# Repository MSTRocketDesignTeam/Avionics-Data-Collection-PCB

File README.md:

# Overview

This repository contains the PCB design files and accompanying firmware for the Data Collection Board of the S&T Rocket Design Team's SRAD Avionics system.

## Purpose and Motivation
The goal of this project is to create flight-rate PCBs that can collect information about the teams rockets as they are launched.

## Inspirations

Initial developments of this board are to be more or less a direct replacement for a Telemetrum V3, with features and design optimizations to be implemented in future revisions.

A [Telemetrum V3](https://altusmetrum.org/TeleMetrum/) is an amateur rocketry telemetry solution from [Altus Metrum](https://altusmetrum.org/index.html).

[Signal](https://bps.space/signal/) from [BPS.Space](https://bps.space/) is a flight computer first and a data collection solution second. It is designed to stream data to the ground station, although it is likely insufficient for the large 10-30k ft class rockets that our team constructs.

There is also a really cool KiCad tutorial around making a small thumb drive sized pcb with an STM32, RF, and USB components. The link is [here on youtube by Phil's Lab](https://www.youtube.com/watch?v=14_jh3nLSsU) and is a great tutorial on using circuit design software and the process/approach you go through making something like this. Highly recommended to watch and maybe take some notes on, and a pretty solid start for our telemetry board.

# Features

#### Physical

#### Primary Components

#### Sensors

#### Data

#### Power

# Companion Documentation

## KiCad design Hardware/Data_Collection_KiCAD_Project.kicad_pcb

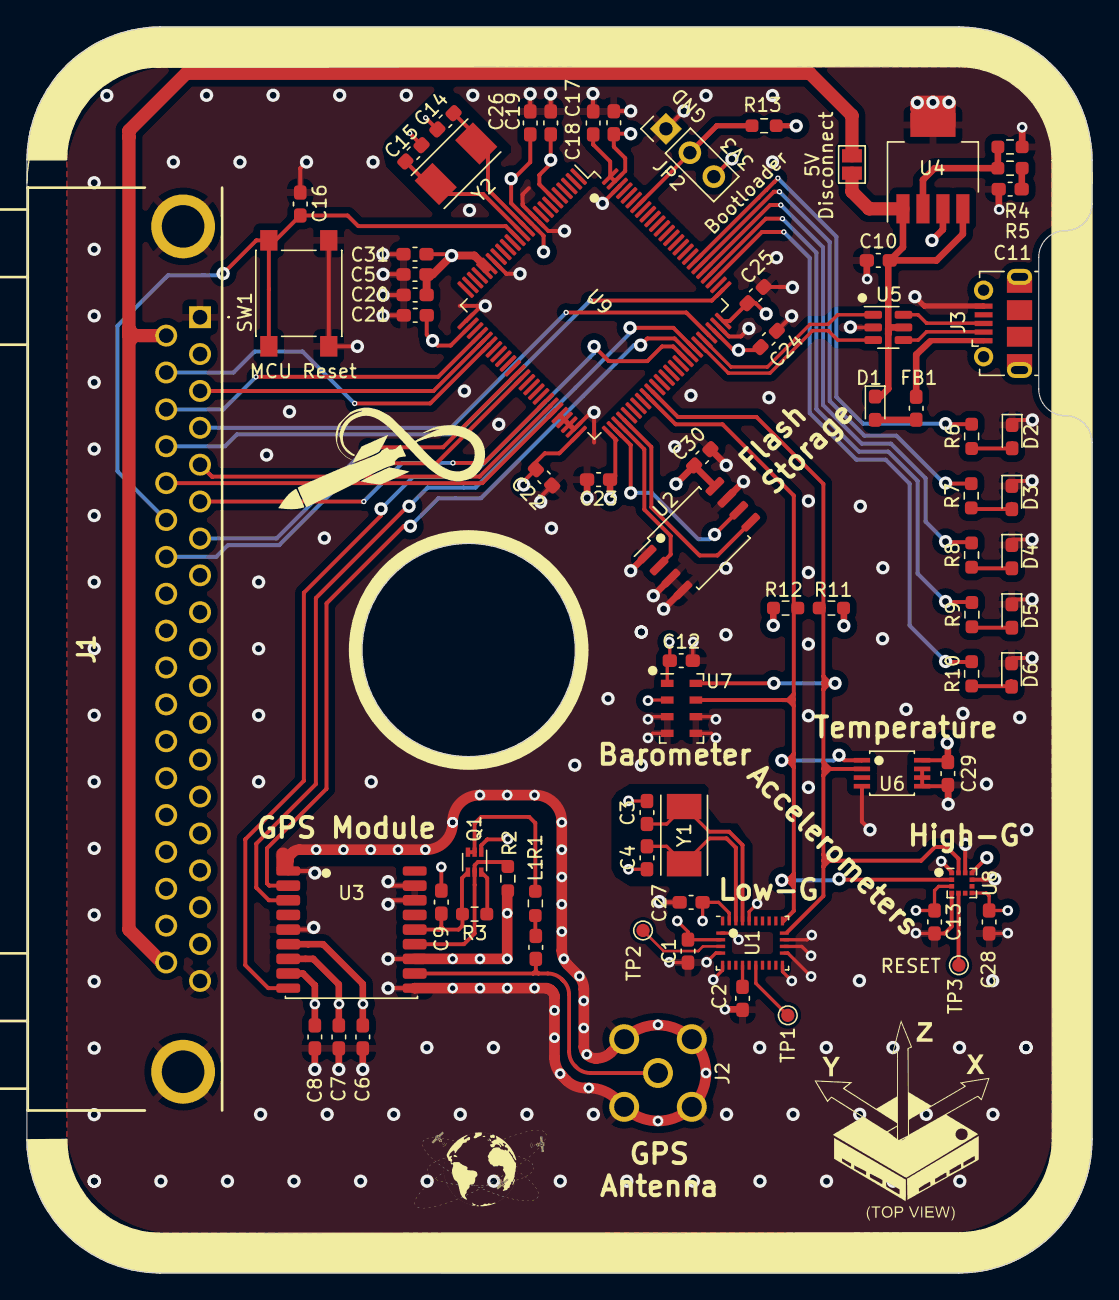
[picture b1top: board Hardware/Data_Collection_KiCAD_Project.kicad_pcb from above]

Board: 4 copper layers, 80.0 x 93.6 mm, 73 parts (0 on the bottom side), 56 nets.

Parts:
C1, C2, C3, C4, C10, C13, C27, C28, C29, C30: 0.1uF; C_0603_1608Metric_Pad1.08x0.95mm_HandSolder
C5, C6, C7, C8, C12, C16, C18, C19, C20, C21, C22, C23, C24, C25: 100nF; C_0603_1608Metric_Pad1.08x0.95mm_HandSolder
C9: 1nF; C_0603_1608Metric_Pad1.08x0.95mm_HandSolder
C11, C17, C26, C31: 1uF; C_0603_1608Metric_Pad1.08x0.95mm_HandSolder
C14, C15: 30pF; C_0603_1608Metric_Pad1.08x0.95mm_HandSolder
D1: D_Schottky_Small; D_0603_1608Metric_Pad1.05x0.95mm_HandSolder
D2, D4, D6: Red; LED_0603_1608Metric_Pad1.05x0.95mm_HandSolder
D3, D5: Grn; LED_0603_1608Metric_Pad1.05x0.95mm_HandSolder
FB1: Ferrite_Bead_Small; C_0603_1608Metric_Pad1.08x0.95mm_HandSolder
J1: L717SDC37P1ACH4F
J2: Conn_Coaxial; SMA_Molex_73251-2200_Horizontal
J3: 10118192-0001LF; USB_Micro-B_Molex-105017-0001
JP1: 5V Disconnect; SolderJumper-2_P1.3mm_Open_Pad1.0x1.5mm
JP2: Debug Jumper; PinHeader_1x03_P2.54mm_Vertical
L1: 27nH; C_0603_1608Metric_Pad1.08x0.95mm_HandSolder
Q1: SI1040X-T1-GE3; SOT-563
R1, R2: 10k; R_0603_1608Metric_Pad0.98x0.95mm_HandSolder
R3: 100k; R_0603_1608Metric_Pad0.98x0.95mm_HandSolder
R4: 390; R_0603_1608Metric_Pad0.98x0.95mm_HandSolder
R5: 240; R_0603_1608Metric_Pad0.98x0.95mm_HandSolder
R6, R7, R8, R9, R10: 820; R_0603_1608Metric_Pad0.98x0.95mm_HandSolder
R11, R12, R13: 4.7k; R_0603_1608Metric_Pad0.98x0.95mm_HandSolder
SW1: MCU Reset; SW_SPST_PTS645
TP1, TP2, TP3: Debug Pad; TestPoint_Pad_D1.0mm
U1: BNO055; LGA-28_5.2x3.8mm_P0.5mm
U2: W25Q32JVSS; SOIC-8_5.23x5.23mm_P1.27mm
U3: MAX-8Q; ublox_MAX
U4: LP38692MPX-ADJ; SOT-223-5
U5: USBLC6-2SC6; SOT-23-6
U6: MIC184YMM-TR
U7: MS5607-02BA; LGA-8_3x5mm_P1.25mm
U8: KX134-1211; LGA-12_2x2mm_P0.5mm
U9: STM32L562VET6Q; LQFP-100_14x14mm_P0.5mm
Y1: 32.768kHz; XTAL_ABM7-32.000MHZ-D2Y-T
Y2: 32MHz; XTAL_ABM7-32.000MHZ-D2Y-T

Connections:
+3V3: C1.2, C5.1, C6.1, C7.1, C8.1, C12.1, C13.1, C17.1, C18.1, C19.1, C20.1, C21.1, C22.1, C23.1, C24.1, C25.1, C26.1, C27.2, C28.1, C29.1, C30.1, C31.1, J1.2, J1.18, JP2.3 (B), R11.2, R12.2, R13.1, U1.3 (VDD), U1.28 (VDDIO), U2.8 (VCC), U3.6 (V_BCKP), U3.7 (VCC_IO), U3.8 (VCC), U4.3 (VOUT), U6.8 (VDD), U7.1 (VDD), U7.2 (PS), U8.3 (IO_VDD), U8.7 (VDD), U8.10 (~CS), U9.6 (VBAT), U9.11 (VDD), U9.20 (VREF+), U9.21 (VDDA), U9.27 (VDD), U9.50 (V15SMPS_1), U9.51 (VDD), U9.73 (VDDUSB), U9.75 (VDD), U9.99 (V15SMPS_2), U9.100 (VDD)
+5V: C10.1, D1.1 (K), JP1.1 (A), U4.1 (EN), U4.4 (VIN), U5.5 (VBUS)
/37 Pin DSUB Bus/Dsub_5v: J1.20, J1.37, JP1.2 (B)
/ABORT_1: J1.7, U9.37 (PE9)
/ABORT_2: J1.26, U9.38 (PE10)
/ALERT_EN: J1.6, U9.43 (PE15)
/ALERT_SCL: J1.5, U9.44 (PB10)
/ALERT_SDA: J1.24, U9.45 (PB11)
/BNO055/~BNO055_BTL: TP2.1, U1.4 (~BOOT_LOAD_PIN)
/BNO055/~BNO055_RESET: TP1.1, U1.11 (~RESET)
/FLASH_CLK: U2.6 (CLK), U9.52 (PB13)
/FLASH_MISO: U2.2 (DO(IO1)), U9.53 (PB14)
/FLASH_MOSI: U2.5 (DI(IO0)), U9.54 (PB15)
/GPS_RX: U3.3 (RXD), U9.69 (PA10)
/GPS_TX: U3.2 (TXD), U9.68 (PA9)
/KX134-1211/KX134_INT1: TP3.1, U8.5 (INT1)
/MAX-8Q/GPS_ANT_NET: J2.1 (In), L1.2, U3.11 (RF_IN)
/MAX-8Q/GPS_LNA_EN: Q1.5 (G1), R2.1, U3.13 (LNA_EN)
/MAX-8Q/GPS_VCC_RF: C9.1, Q1.4 (S2), R3.2, U3.14 (VCC_RF)
/NRST: C16.1, J1.25, SW1.1, U9.14 (NRST)
/SENSOR_SCL: R11.1, U1.19 (COM1), U6.2 (CLK), U7.8 (SCLK), U8.12 (SCLK/SCL), U9.60 (PD13)
/SENSOR_SDA: R12.1, U1.20 (COM0), U6.1 (DATA), U7.7 (SDI/SDA), U8.2 (SDI/SDA), U9.59 (PD12)
/SWCLK: J1.23, U9.76 (PA14)
/SWDIO: J1.4, U9.72 (PA13)
/TELEMETRY_MISO: J1.3, U9.30 (PA6)
/TELEMETRY_MOSI: J1.21, U9.31 (PA7)
/TELEMETRY_SCK: J1.22, U9.29 (PA5)
/USB Connector and ESD/USB_CONN_D+: J3.3, U5.6 (I/O1)
/USB Connector and ESD/USB_CONN_D-: J3.2, U5.4 (I/O2)
/USB_D+: U5.1 (I/O1), U9.71 (PA12)
/USB_D-: U5.3 (I/O2), U9.70 (PA11)
/~GPS_RESET: U3.9 (~RESET), U9.67 (PA8)
GND: C1.1, C2.1, C3.1, C4.1, C5.2, C6.2, C7.2, C8.2, C9.2, C10.2, C11.2, C12.2, C13.2, C14.2, C15.2, C16.2, C17.2, C18.2, C19.2, C20.2, C21.2, C22.2, C23.2, C24.2, C25.2, C26.2, C27.1, C28.2, C29.2, C30.2, C31.2, D2.1 (K), D3.1 (K), D4.1 (K), D5.1 (K), D6.1 (K), J1.1, J1.19, J1.MH1, J1.MH2, J2.2 (Ext), J3.5, JP2.1 (A), Q1.1 (S1), R2.2, R4.2, SW1.2, U1.2 (GND), U1.5 (PS1), U1.6 (PS0), U1.15 (GNDIO), U1.16 (GNDIO), U1.17 (COM3), U1.18 (COM2), U1.25 (GNDIO), U2.1 (~CS), U2.3 (IO2), U2.4 (GND), U2.7 (IO3), U3.1 (GND), U3.5 (EXTINT), U3.10 (GND), U3.12 (GND), U3.16 (SDA), U3.17 (SCL), U4.5 (GND), U5.2 (GND), U6.4 (GND), U6.5 (A2/T1), U6.6 (A1), U6.7 (A0), U7.3 (GND), U7.4 (CSB), U7.5 (CSB), U7.6 (SDO), U8.1 (SDO/ADDR), U8.4 (TRIG), U8.9 (GND), U8.11 (NC), U9.10 (VSS), U9.19 (VREF-/VSSA), U9.26 (VSS), U9.46 (VDDSMPS), U9.47 (VLXSMPS), U9.48 (VSSSMPS), U9.49 (VSS), U9.74 (VSS), U9.98 (VSS)
unnamed: C2.2, U1.9 (CAP)
unnamed: C3.2, U1.26 (XOUT32), Y1.1
unnamed: C4.2, U1.27 (XIN32), Y1.2
unnamed: C11.1, R5.1
unnamed: C14.1, U9.12 (PH0), Y2.1
unnamed: C15.1, U9.13 (PH1), Y2.2
unnamed: D1.2 (A), FB1.1
unnamed: D2.2 (A), R6.1
unnamed: D3.2 (A), R7.1
unnamed: D4.2 (A), R8.1
unnamed: D5.2 (A), R9.1
unnamed: D6.2 (A), R10.1
unnamed: FB1.2, J3.1
unnamed: L1.1, R1.2
unnamed: Q1.2 (D2), Q1.3 (D2), R1.1
unnamed: Q1.6 (D1), R3.1
unnamed: R4.1, R5.2, U4.2 (ADJ)
unnamed: R10.2, U9.78 (PC10)
unnamed: R9.2, U9.79 (PC11)
unnamed: R8.2, U9.80 (PC12)
unnamed: R7.2, U9.81 (PD0)
unnamed: R6.2, U9.82 (PD1)
unnamed: JP2.2 (C), R13.2, U9.94 (PH3)

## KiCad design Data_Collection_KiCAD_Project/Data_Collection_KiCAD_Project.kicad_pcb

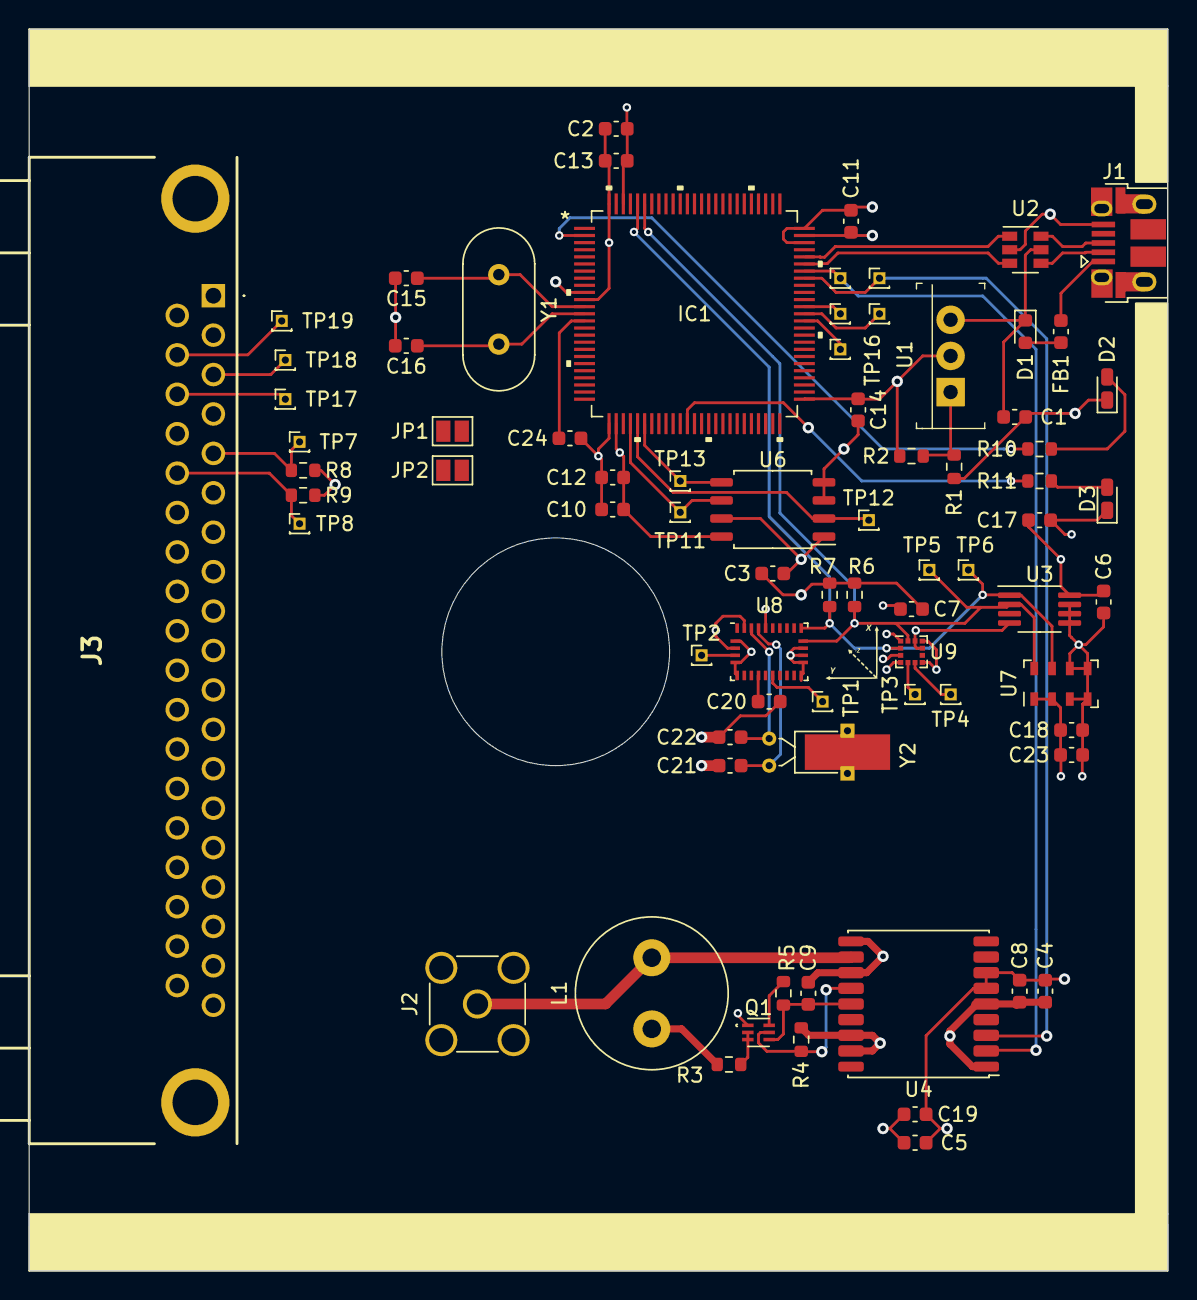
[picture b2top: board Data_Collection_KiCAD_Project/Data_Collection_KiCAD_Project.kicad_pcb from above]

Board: 4 copper layers, 80.0 x 87.2 mm, 76 parts (0 on the bottom side), 50 nets.

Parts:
C1, C19, C20, C21, C22, C23: 0.1uF; C_0603_1608Metric
C2, C4, C10: 1uF; C_0603_1608Metric
C3, C5, C6, C7, C8, C11, C12, C13, C14, C17, C18, C24: 100nF; C_0603_1608Metric
C9: 1nF; C_0603_1608Metric
C15, C16: 30pF; C_0603_1608Metric
D1: D_Schottky; D_0603_1608Metric
D2: Green; D_0603_1608Metric_Castellated
D3: Red; D_0603_1608Metric_Castellated
FB1: Ferrite_Bead_Small; C_0603_1608Metric
IC1: STM32L562VET6Q
J1: USB_B_Micro; USB_Micro-B_Amphenol_10103594-0001LF_Horizontal
J2: Conn_Coaxial; SMA_Amphenol_132134-11_Vertical
J3: L717SDC37P1ACH4F
JP1: VDDA Bridge; SolderJumper-2_P1.3mm_Open_Pad1.0x1.5mm
JP2: VDD_SMPS; SolderJumper-2_P1.3mm_Open_Pad1.0x1.5mm
L1: 27nH; L_Radial_D10.5mm_P5.00mm_Abacron_AISR-01
Q1: SI1040X-T1-GE3; SC-89
R1: 390; R_0603_1608Metric
R2: 240; R_0603_1608Metric
R3, R4: 10k; R_0603_1608Metric
R5: 100k; R_0603_1608Metric
R6, R7: 4.7K; R_0603_1608Metric
R8, R9: DNP; R_0603_1608Metric
R10, R11: 80; R_0603_1608Metric
TP1, TP2, TP3, TP4, TP5, TP6, TP7, TP8, TP9, TP10, TP11, TP12, TP13, TP14, TP15, TP16, TP17, TP18, TP19: Debug Pad; PinHeader_1x01_P1.00mm_Vertical
U1: LM317T; TO-220-3
U2: USBLC6-2SC6; SOT-23-6
U3: MCP9808_MSOP; MSOP-8_3x3mm_P0.65mm
U4: MAX-8Q; ublox_MAX
U6: W25Q32JVSS; SOIC-8_5.23x5.23mm_P1.27mm
U7: MS5607-02BA; LGA-8_3x5mm_P1.25mm
U8: BNO055; LGA-28_5.2x3.8mm_P0.5mm
U9: KX134-1211; LGA-12_2x2mm_P0.5mm
Y1: 32MHz; Crystal_HC49-4H_Vertical
Y2: 32.768kHz; Crystal_DS26_D2.0mm_L6.0mm_Horizontal_1EP_style2

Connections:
+3V3: C2.1, C3.1, C4.1, C5.1, C6.1, C7.1, C8.1, C10.1, C11.1, C12.1, C13.1, C14.1, C17.1, C18.1, C19.2, C23.2, IC1.11, IC1.27, IC1.51, IC1.73, IC1.75, IC1.100, J3.2, J3.18, JP1.2, JP2.1, R2.1, R6.2, R7.2, R8.2, R9.2, U1.2, U3.8, U4.6, U4.7, U4.8, U6.8, U7.1, U7.2, U8.3, U8.28, U9.3, U9.7, U9.10
+5V: C1.1, D1.1, J3.20, J3.37, U1.3, U2.5
/BNO055/~BNO055_BTL: TP2.1, U8.4
/BNO055/~BNO055_RESET: TP1.1, U8.11
/EXT_SCL: IC1.44, J3.5, R8.1, TP7.1
/EXT_SDA: IC1.45, J3.24, R9.1, TP8.1
/I2C1_SCL: IC1.95, R6.1, TP5.1, U3.2, U7.8, U8.19, U9.12
/I2C1_SDA: IC1.96, R7.1, TP6.1, U3.1, U7.7, U8.20, U9.2
/I2C_ALERT: IC1.32, J3.6
/KX134-1211/KX134_INT1: TP3.1, U9.5
/KX134-1211/KX134_INT2: TP4.1, U9.6
/MAX-8Q/GPS_ANT_NET: J2.1, L1.2, U4.11
/MAX-8Q/GPS_LNA_EN: Q1.5, R4.1, U4.13
/MAX-8Q/GPS_VCC_RF: C9.1, Q1.4, R5.2, U4.14
/NRST: C24.1, IC1.14, J3.25
/SPI1_MISO: IC1.30, TP12.1, U6.2
/SPI1_MOSI: IC1.31, TP13.1, U6.5
/SPI1_SCK: IC1.29, TP11.1, U6.6
/SPI2_MISO: IC1.53, J3.3, TP18.1
/SPI2_MOSI: IC1.54, J3.21, TP19.1
/SPI2_SCK: IC1.52, J3.22, TP17.1
/SWCLK: IC1.76, J3.23
/SWDIO: IC1.72, J3.4
/USART1_RX: IC1.69, TP10.1, U4.2
/USART1_TX: IC1.68, TP9.1, U4.3
/USB Connector and ESD/USB_CONN_D+: J1.3, U2.6
/USB Connector and ESD/USB_CONN_D-: J1.2, U2.4
/USB_D+: IC1.71, U2.1
/USB_D-: IC1.70, U2.3
GND: C1.2, C2.2, C3.2, C4.2, C5.2, C6.2, C7.2, C8.2, C9.2, C10.2, C11.2, C12.2, C13.2, C14.2, C15.2, C16.2, C17.2, C18.2, C19.1, C20.1, C21.1, C22.1, C23.1, C24.2, D2.1, D3.1, IC1.10, IC1.26, IC1.48, IC1.49, IC1.74, IC1.98, J1.5, J2.2, J3.1, J3.19, J3.MH1, J3.MH2, Q1.1, R1.2, R4.2, U2.2, U3.4, U3.5, U3.6, U3.7, U4.1, U4.5, U4.10, U4.12, U4.16, U4.17, U6.1, U6.3, U6.4, U6.7, U7.3, U7.4, U7.5, U7.6, U8.2, U8.5, U8.6, U8.15, U8.16, U8.17, U8.18, U8.25, U9.1, U9.4, U9.9, U9.11
unnamed: C15.1, IC1.12, Y1.1
unnamed: C16.1, IC1.13, Y1.2
unnamed: C20.2, U8.9
unnamed: C21.2, U8.26, Y2.1
unnamed: C22.2, U8.27, Y2.2
unnamed: D1.2, FB1.1
unnamed: D2.2, R10.2
unnamed: D3.2, R11.2
unnamed: FB1.2, J1.1
unnamed: IC1.2, R10.1
unnamed: IC1.21, JP1.1
unnamed: IC1.37, R11.1
unnamed: IC1.46, JP2.2
unnamed: IC1.62, TP16.1
unnamed: IC1.63, TP15.1
unnamed: IC1.64, TP14.1
unnamed: L1.1, R3.2
unnamed: Q1.2, Q1.3, R3.1
unnamed: Q1.6, R5.1
unnamed: R1.1, R2.2, U1.1

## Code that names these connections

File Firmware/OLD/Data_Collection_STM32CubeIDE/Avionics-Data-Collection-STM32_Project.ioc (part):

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Mcu.Name=STM32L562VETxQ
Mcu.Package=LQFP100
Mcu.UserName=STM32L562VETxQ
PA10.Mode=Asynchronous
PA10.Signal=USART1_RX
PA11.Mode=Device
PA11.Signal=USB_DM
PA12.Mode=Device
PA12.Signal=USB_DP
PA13\ (JTMS/SWDIO).Mode=Serial_Wire
PA13\ (JTMS/SWDIO).Signal=DEBUG_JTMS-SWDIO
PA14\ (JTCK/SWCLK).Mode=Serial_Wire
PA14\ (JTCK/SWCLK).Signal=DEBUG_JTCK-SWCLK
PA5.GPIOParameters=GPIO_Label
PA5.GPIO_Label=SPI2_SCK
PA5.Mode=Full_Duplex_Master
PA5.Signal=SPI1_SCK
PA6.GPIOParameters=GPIO_Label
PA6.GPIO_Label=SPI2_MISO
PA6.Mode=Full_Duplex_Master
PA6.Signal=SPI1_MISO
PA7.GPIOParameters=GPIO_Label
PA7.GPIO_Label=SPI2_MOSI
PA7.Mode=Full_Duplex_Master
PA7.Signal=SPI1_MOSI
PA9.Mode=Asynchronous
PA9.Signal=USART1_TX
PB10.Mode=I2C
PB10.Signal=I2C2_SCL
PB11.Mode=I2C
PB11.Signal=I2C2_SDA
PB13.GPIOParameters=GPIO_Label
PB13.GPIO_Label=SPI1_SCK
PB13.Mode=Full_Duplex_Master
PB13.Signal=SPI2_SCK
PB14.GPIOParameters=GPIO_Label
PB14.GPIO_Label=SPI1_MISO
PB14.Mode=Full_Duplex_Master
PB14.Signal=SPI2_MISO
PB15.GPIOParameters=GPIO_Label
PB15.GPIO_Label=SPI1_MOSI
PB15.Mode=Full_Duplex_Master
PB15.Signal=SPI2_MOSI
PD12.GPIOParameters=GPIO_Label
PD12.GPIO_Label=I2C1_SCL
PD12.Mode=I2C
PD12.Signal=I2C4_SCL
PD13.GPIOParameters=GPIO_Label
PD13.GPIO_Label=I2C1_SDA
PD13.Mode=I2C
PD13.Signal=I2C4_SDA
PE10.GPIOParameters=GPIO_Label
PE10.GPIO_Label=Abort_2
PE10.Signal=GPIO_Input
PE15.GPIOParameters=GPIO_Label
PE15.GPIO_Label=I2C2_EN
PE15.Signal=GPIO_Input
PE3.Signal=S_TIM3_CH1
PE9.GPIOParameters=GPIO_Label
PE9.GPIO_Label=Abort_1
PE9.Signal=GPIO_Input
PH0-OSC_IN\ (PH0).Mode=HSE-External-Oscillator
PH0-OSC_IN\ (PH0).Signal=RCC_OSC_IN
PH1-OSC_OUT\ (PH1).Mode=HSE-External-Oscillator
PH1-OSC_OUT\ (PH1).Signal=RCC_OSC_OUT
RCC.HSE_VALUE=32000000
RCC.SYSCLKFreq_VALUE=96000000
RCC.SYSCLKSource=RCC_SYSCLKSOURCE_PLLCLK
board=custom

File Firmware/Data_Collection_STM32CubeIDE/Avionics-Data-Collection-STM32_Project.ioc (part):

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Mcu.Name=STM32L562VETxQ
Mcu.Package=LQFP100
Mcu.UserName=STM32L562VETxQ
PA10.Mode=Asynchronous
PA10.Signal=USART1_RX
PA11.Mode=Device
PA11.Signal=USB_DM
PA12.Mode=Device
PA12.Signal=USB_DP
PA13\ (JTMS/SWDIO).Mode=Serial_Wire
PA13\ (JTMS/SWDIO).Signal=DEBUG_JTMS-SWDIO
PA14\ (JTCK/SWCLK).Mode=Serial_Wire
PA14\ (JTCK/SWCLK).Signal=DEBUG_JTCK-SWCLK
PA5.GPIOParameters=GPIO_Label
PA5.GPIO_Label=SPI2_SCK
PA5.Mode=Full_Duplex_Master
PA5.Signal=SPI1_SCK
PA6.GPIOParameters=GPIO_Label
PA6.GPIO_Label=SPI2_MISO
PA6.Mode=Full_Duplex_Master
PA6.Signal=SPI1_MISO
PA7.GPIOParameters=GPIO_Label
PA7.GPIO_Label=SPI2_MOSI
PA7.Mode=Full_Duplex_Master
PA7.Signal=SPI1_MOSI
PA9.Mode=Asynchronous
PA9.Signal=USART1_TX
PB10.Mode=I2C
PB10.Signal=I2C2_SCL
PB11.Mode=I2C
PB11.Signal=I2C2_SDA
PC10.GPIOParameters=GPIO_Label
PC10.GPIO_Label=SPI1_SCK
PC10.Mode=Full_Duplex_Master
PC10.Signal=SPI3_SCK
PC11.GPIOParameters=GPIO_Label
PC11.GPIO_Label=SPI1_MISO
PC11.Mode=Full_Duplex_Master
PC11.Signal=SPI3_MISO
PC12.GPIOParameters=GPIO_Label
PC12.GPIO_Label=SPI1_MOSI
PC12.Mode=Full_Duplex_Master
PC12.Signal=SPI3_MOSI
PD12.GPIOParameters=GPIO_Label
PD12.GPIO_Label=I2C1_SCL
PD12.Mode=I2C
PD12.Signal=I2C4_SCL
PD13.GPIOParameters=GPIO_Label
PD13.GPIO_Label=I2C1_SDA
PD13.Mode=I2C
PD13.Signal=I2C4_SDA
PE3.Signal=S_TIM3_CH1
PE9.Signal=S_TIM1_CH1
PH0-OSC_IN\ (PH0).Mode=HSE-External-Oscillator
PH0-OSC_IN\ (PH0).Signal=RCC_OSC_IN
PH1-OSC_OUT\ (PH1).Mode=HSE-External-Oscillator
PH1-OSC_OUT\ (PH1).Signal=RCC_OSC_OUT
RCC.HSE_VALUE=32000000
RCC.SYSCLKFreq_VALUE=96000000
RCC.SYSCLKSource=RCC_SYSCLKSOURCE_PLLCLK
board=custom

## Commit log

2021-09-30 Create LICENSE
2021-10-01 Schematic v1.0.0
    Creation of KiCAD project file, initial draft of PCB schematic file, components chosen as a starting point and will likely be altered in future revisions.
2021-10-01 Schematic v1.0.1
    Organized schematic into separate sheets. This helps modularize the project and eases switching between components as the design progresses.
2021-10-01 Schematic v1.0.2
    Moved MCU to separate sheet.
2021-10-03 Schematic v1.0.3
    Reorganized the main page to use bus lines.
2021-10-03 Schematic v1.0.4
    Added I2C addresses to MEMS, Temp Sensor, and Barometer on main schematic page.
2021-10-11 Schematic v1.0.5
    Added 64G capable Accelerometer.
    Replaced ICM-20948 with BNO055 for 3.3V I2C compatibility.
    Things to do: Add I2C pullup resistors for entire bus, Route INT pins to uC.
2021-10-13 Re-Added MEMS_ICM-20948.sch
    Re-added schematic file in case there is need in the future.
2021-10-13 Separated BNO055 and KX134
    Separated the hierarchical sheets for the BNO055 IMU and KX134 High G-Accelerometer.
2021-10-13 Starting Assigning Pins and Messed with Crystal Scalers
    - Started to pin physical pin assignments in the pinout view to show a graphical representation of which pins are available.
    - Enabled the high speed external crystal and configured PLL scalers to create a 48MHz signal for USB and 96MHz signal for main core. (if power consumption is an issue we can change this)
2021-10-13 Updated Firmware?
    Was prompted to update to latest firmware.
2021-10-28 Formatting
    Misc Formatting and CubeIDE configuration.
    Also Added datasheets folder
2021-11-01 Added Main Bus Layout
    added main bus connector and connected various pins
    TODO:
    -Implement I2C interrupt pin
    -Add I2C Pullups
    -Add I2C Capacitors
    -Check for auxiliary pins needed from sensors
2021-11-03 Added Power Budget Spreadsheet
    TODO:
    -Implement I2C interrupt pin
    -Add I2C Pullups
    -Add I2C Capacitors
    -Check for auxiliary pins needed from sensors
    -Add power buffer cap and diode?
2021-11-03 Update sym-lib-table
2021-11-17 Added Main Bus Card Edge Connector Sheet
2021-11-18 Fixed Component Libraries
    Changed over from project specific to global libraries.
2021-11-18 Library Issues Resolved
    I discovered that project specific library paths were causing issues when swapping between computers so I removed all project specific libraries and added the sparkfun and digikey libs to my global l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
2021-11-23 i2c Pullups added
2021-11-23 Added Resistors for LED
2021-11-24 footprint and value changes
2021-11-24 Added 37Pin DSUB Main Bus
2021-11-24 Corrected Main Bus Connector
2021-11-29 footprint changes
2021-12-01 Finalized Schematic
2021-12-01 Changed MCU and started pcb
2021-12-01 PCB Progress
2021-12-02 progress update
2021-12-02 Finished laying out PCB Components
2021-12-02 routed signal traces
2021-12-02 routing update
2021-12-02 Routing Almost Finalized
2021-12-06 Reformatted repo
2021-12-06 Reformatted repo more
2021-12-07 GPS layout change and test point tweaks
2021-12-07 Finalized
    Everything is routed. There are probably some things that need rerouting or adjustment.
2021-12-21 Schematic Tweaks and Board Dimensioned
2021-12-21 routing progress and pin reassignment
2021-12-21 Routing Progress
2021-12-21 finished routing
2022-01-24 Updated file format to KiCAD v6, replaced voltage regulator
2022-01-24 Added 3D models to components
2022-01-24 Updated MCU Component Sheet
    Used the file from the Telemetry board for compatibility and commonality.
2022-01-24 Corrected PCB edge cuts, removed components
    Will be mimicking layout done by Seth Sievers
2022-01-25 Organized components, arranged filter caps
2022-01-25 Added silkscreen art
2022-01-25 Added signatures to silkscreen
2022-01-28 wtf is wrong with my github install
2022-01-29 fixed it
2022-01-29 almost there
2022-01-30 almost almost there
2022-01-30 Replaced Temp Sense and finalized routing
2022-01-30 I think it is done....
    maybe
    hopefully
    please
2022-01-31 should be done now
    DRC is angry about some minor via tolerance issues (pad to pad clearance) which are out of JLC specifications but they don't make any sense on their website so I think they can manufacture them just 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
2022-01-31 Corrected Si-1040X Footprint
    Canged from TSOT-23-6 to SOT-563 (Called SC-89-6 in datasheet)
2022-01-31 Improved data line separation, added ground stitching vias
2022-01-31 Added silkscreen art, adjusted copper pour clearances
2022-01-31 Added more silkscreen art
2022-01-31 Corrected Si1040X Footprint
2022-02-01 fixed broken layer fill
    pad was unconnected due to DRC violation due to copper pour keep out zone.
2022-02-07 Corrected silkscreen qr code
2022-02-12 Repositioned sensors to accommodate GPS connector relocation
2022-02-12 Added cutout for USB connector
2022-02-13 Changed 3D models from .wrl to .step
2022-02-19 Changed hole location
    Hole was moved over 2mm for adjust for tollerences
2022-02-19 Previous change
    didnt push, so now i am
2022-02-27 Updated .gitignore to remove KiCAD backup files
2022-02-28 Corrected Board Edge Cuts
2022-02-28 Aligned components to new board dimensions, adjusted silkscreen border, aligned center hole
    Some traces need to be corrected around the center hole still
2022-02-28 Added dimensions for center hole to user drawings layer
2022-02-28 Adjusted position of QR Code
2022-03-02 Optimized spacings, via stitching, added right angle sma w/ male
2022-03-05 Adjusted component spacing, corrected MCU schematic, added cutout for USB, moved SMA inwards
2022-03-05 Adjusted silkscreen identifiers
2022-03-07 Adjusted Silkscreen
2022-03-18 Generated gerb
    Gerb and drill files were generated
2022-03-18 updated board and gerbs
    JLC didnt like our stuff so landmarks were changed to account for this.
2022-05-07 New code
2022-05-08 redid stmcubeide
2022-05-26 work on code, still a mess of tests

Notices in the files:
parts and their libraries:
Copyright 2021 Accelerated Designs. All rights reserved.
